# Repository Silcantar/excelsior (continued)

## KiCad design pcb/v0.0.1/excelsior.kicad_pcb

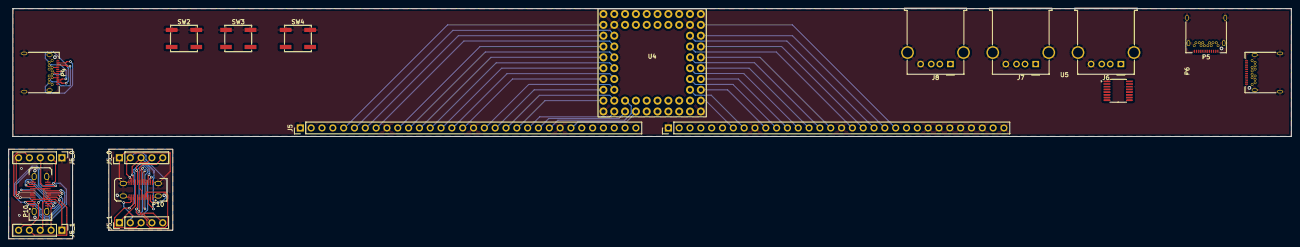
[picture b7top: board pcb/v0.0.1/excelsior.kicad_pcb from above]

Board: 2 copper layers, 301.0 x 54.0 mm, 19 parts (0 on the bottom side), 74 nets.

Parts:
J5: Conn_01x40_Socket; PinHeader_1x32_P2.54mm_Vertical
J5_0, J5_0#2, J5_1, J5_1#2: Conn_01x12; PinHeader_1x05_P2.54mm_Vertical
J6: USB_Hub4_FDD; USB_A_Molex_67643_Horizontal
J7: USB_Hub3; USB_A_Molex_67643_Horizontal
J8: USB_Hub2; USB_A_Molex_67643_Horizontal
J9: Conn_01x16_Socket; PinHeader_1x32_P2.54mm_Vertical
P4: Left_Peripheral; USB_C_Receptacle_Amphenol_12401548E4-2A
P5: Host_Port; USB_C_Receptacle_Amphenol_12401548E4-2A
P6: Right_Peripheral; USB_C_Receptacle_Amphenol_12401548E4-2A
P10, P10#2: USB_C_Receptacle; USB_C_Receptacle_JAE_DX07S024WJ3R400
SW2, SW3, SW4: SW_Push; SW_SPST_EVPBF
U4: PGA2350; pga2350
U5: CH334R; QSOP-16_3.9x4.9mm_P0.635mm

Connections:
/Excelsior_PGA2350/3V3: J9.31, U4.3V3
/Excelsior_PGA2350/BOOT: SW4.2, U4.BS (BOOTSEL)
/Excelsior_PGA2350/CH_RST: SW2.2, U5.9 (~RESET/CDP)
/Excelsior_PGA2350/CS: J5.8, P4.A3 (TX1-), P4.B3 (TX2-), P6.A3 (TX1-), P6.B3 (TX2-), U4.05 (GP05)
/Excelsior_PGA2350/DM1+: U4.U+ (USB_D+), U5.8 (DP1+)
/Excelsior_PGA2350/DM1-: U4.U- (USB_D-), U5.7 (DM1-)
/Excelsior_PGA2350/DM2+: J8.3 (D+), U5.6 (DP2+)
/Excelsior_PGA2350/DM2-: J8.2 (D-), U5.5 (DM2-)
/Excelsior_PGA2350/DM3+: J7.3 (D+), U5.4 (DP3+)
/Excelsior_PGA2350/DM3-: J7.2 (D-), U5.3 (DM3-)
/Excelsior_PGA2350/DM4+: J6.3 (D+), U5.2 (DP4+)
/Excelsior_PGA2350/DM4-: J6.2 (D-), U5.1 (DM4-)
/Excelsior_PGA2350/GND: J5.1, J5.9, J5.17, J5.25, J6.4 (GND), J6.5 (Shield), J7.4 (GND), J7.5 (Shield), J8.4 (GND), J8.5 (Shield), J9.1, J9.9, J9.17, J9.25, J9.26, J9.27, J9.28, J9.29, J9.30, J9.32, P4.A1 (GND), P4.A12 (GND), P4.B1 (GND), P4.B12 (GND), P4.S1 (SHIELD), P5.A1 (GND), P5.A12 (GND), P5.B1 (GND), P5.B12 (GND), P5.S1 (SHIELD), P6.A1 (GND), P6.A12 (GND), P6.B1 (GND), P6.B12 (GND), P6.S1 (SHIELD), SW2.1, SW3.1, SW4.1, U4.G (GND), U5.14 (GND)
/Excelsior_PGA2350/GP06: J5.10, U4.06 (GP06)
/Excelsior_PGA2350/GP07: J5.11, U4.07 (GP07)
/Excelsior_PGA2350/GP08: J5.12, U4.08 (GP08)
/Excelsior_PGA2350/GP09: J5.13, U4.09 (GP09)
/Excelsior_PGA2350/GP10: J5.14, U4.10 (GP10)
/Excelsior_PGA2350/GP11: J5.15, U4.11 (GP11)
/Excelsior_PGA2350/GP12: J5.16, U4.12 (GP12)
/Excelsior_PGA2350/GP13: J5.18, U4.13 (GP13)
/Excelsior_PGA2350/GP14: J5.19, U4.14 (GP14)
/Excelsior_PGA2350/GP15: J5.20, U4.15 (GP15)
/Excelsior_PGA2350/GP16: J5.21, U4.16 (GP16)
/Excelsior_PGA2350/GP17: J5.22, U4.17 (GP17)
/Excelsior_PGA2350/GP18: J5.23, U4.18 (GP18)
/Excelsior_PGA2350/GP19: J5.24, U4.19 (GP19)
/Excelsior_PGA2350/GP20: J5.26, U4.20 (GP20)
/Excelsior_PGA2350/GP21: J5.27, U4.21 (GP21)
/Excelsior_PGA2350/GP22: J5.28, U4.22 (GP22)
/Excelsior_PGA2350/GP23: J5.29, U4.23 (GP23)
/Excelsior_PGA2350/GP24: J5.30, U4.24 (GP24)
/Excelsior_PGA2350/GP25: J5.31, U4.25 (GP25)
/Excelsior_PGA2350/GP26: J5.32, U4.26 (GP26)
/Excelsior_PGA2350/GP27: J9.2, U4.27 (GP27)
/Excelsior_PGA2350/GP28: J9.3, U4.28 (GP28)
/Excelsior_PGA2350/GP29: J9.4, U4.29 (GP29)
/Excelsior_PGA2350/GP30: J9.5, U4.30 (GP30)
/Excelsior_PGA2350/GP31: J9.6, U4.31 (GP31)
/Excelsior_PGA2350/GP32: J9.7, U4.32 (GP32)
/Excelsior_PGA2350/GP33: J9.8, U4.33 (GP33)
/Excelsior_PGA2350/GP34: J9.10, U4.34 (GP34)
/Excelsior_PGA2350/GP35: J9.11, U4.35 (GP35)
/Excelsior_PGA2350/GP36: J9.12, U4.36 (GP36)
/Excelsior_PGA2350/GP37: J9.13, U4.37 (GP37)
/Excelsior_PGA2350/GP38: J9.14, U4.38 (GP38)
/Excelsior_PGA2350/GP39: J9.15, U4.39 (GP39)
/Excelsior_PGA2350/GP40: J9.16, U4.40 (GP40)
/Excelsior_PGA2350/GP41: J9.18, U4.41 (GP41)
/Excelsior_PGA2350/GP42: J9.19, U4.42 (GP42)
/Excelsior_PGA2350/GP43: J9.20, U4.43 (GP43)
/Excelsior_PGA2350/GP44: J9.21, U4.44 (GP44)
/Excelsior_PGA2350/GP45: J9.22, U4.45 (GP45)
/Excelsior_PGA2350/GP46: J9.23, U4.46 (GP46)
/Excelsior_PGA2350/GP47: J9.24, U4.47 (GP47)
/Excelsior_PGA2350/HOST_D+: P5.A6 (D+), P5.B6 (D+), U5.11 (DPU+)
/Excelsior_PGA2350/HOST_D-: P5.A7 (D-), P5.B7 (D-), U5.10 (DMU-)
/Excelsior_PGA2350/INTA: J5.3, P4.A10 (RX2-), P4.B10 (RX1-), P6.A10 (RX2-), P6.B10 (RX1-), U4.00 (GP00)
/Excelsior_PGA2350/INTB: J5.4, P4.A11 (RX2+), P4.B11 (RX1+), P6.A11 (RX2+), P6.B11 (RX1+), U4.01 (GP01)
/Excelsior_PGA2350/MISO: J5.7, P4.A6 (D+), P4.B6 (D+), P6.A6 (D+), P6.B6 (D+), U4.04 (GP04)
/Excelsior_PGA2350/MOSI: J5.6, P4.A7 (D-), P4.B7 (D-), P6.A7 (D-), P6.B7 (D-), U4.03 (GP03)
/Excelsior_PGA2350/RESET: SW3.2, U4.R (RUN)
/Excelsior_PGA2350/SCK: J5.5, P4.A2 (TX1+), P4.B2 (TX2+), P6.A2 (TX1+), P6.B2 (TX2+), U4.02 (GP02)
/Excelsior_PGA2350/VBUS: J5.2, J6.1 (VBUS), J7.1 (VBUS), J8.1 (VBUS), P4.A4 (VBUS), P4.A9 (VBUS), P4.B4 (VBUS), P4.B9 (VBUS), P5.A4 (VBUS), P5.A9 (VBUS), P5.B4 (VBUS), P5.B9 (VBUS), P6.A4 (VBUS), P6.A9 (VBUS), P6.B4 (VBUS), P6.B9 (VBUS), U4.3EN (3V3_EN), U4.VBB (VBUS), U5.12 (V5)
/USB Breakout/2: J5_0.2, J5_0#2.2, P10.A2 (TX1+), P10.B2 (TX2+), P10#2.A2 (TX1+), P10#2.B2 (TX2+)
/USB Breakout/3: J5_0.3, J5_0#2.3, P10.A3 (TX1-), P10.B3 (TX2-), P10#2.A3 (TX1-), P10#2.B3 (TX2-)
/USB Breakout/5: J5_0.4, J5_0#2.4, P10.A5 (CC1), P10.B5 (CC2), P10#2.A5 (CC1), P10#2.B5 (CC2)
/USB Breakout/6: J5_0.5, J5_0#2.5, P10.A6 (D+), P10.B6 (D+), P10#2.A6 (D+), P10#2.B6 (D+)
/USB Breakout/7: J5_1.5, J5_1#2.5, P10.A7 (D-), P10.B7 (D-), P10#2.A7 (D-), P10#2.B7 (D-)
/USB Breakout/8: J5_1.4, J5_1#2.4, P10.A8 (SBU1), P10.B8 (SBU2), P10#2.A8 (SBU1), P10#2.B8 (SBU2)
/USB Breakout/10: J5_1.3, J5_1#2.3, P10.A10 (RX2-), P10.B10 (RX1-), P10#2.A10 (RX2-), P10#2.B10 (RX1-)
/USB Breakout/11: J5_1.2, J5_1#2.2, P10.A11 (RX2+), P10.B11 (RX1+), P10#2.A11 (RX2+), P10#2.B11 (RX1+)
/USB Breakout/GND: J5_0.1, J5_0#2.1, P10.A1 (GND), P10.A12 (GND), P10.B1 (GND), P10.B12 (GND), P10.S1 (SHIELD), P10#2.A1 (GND), P10#2.A12 (GND), P10#2.B1 (GND), P10#2.B12 (GND), P10#2.S1 (SHIELD)
/USB Breakout/VBUS: J5_1.1, J5_1#2.1, P10.A4 (VBUS), P10.A9 (VBUS), P10.B4 (VBUS), P10.B9 (VBUS), P10#2.A4 (VBUS), P10#2.A9 (VBUS), P10#2.B4 (VBUS), P10#2.B9 (VBUS)

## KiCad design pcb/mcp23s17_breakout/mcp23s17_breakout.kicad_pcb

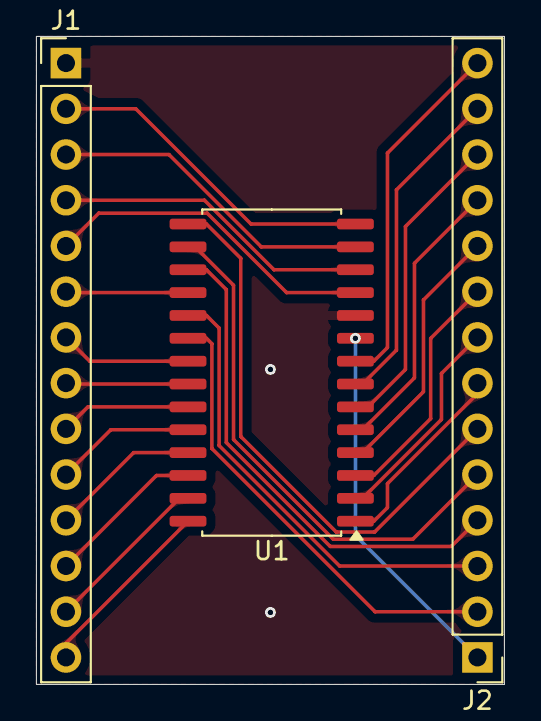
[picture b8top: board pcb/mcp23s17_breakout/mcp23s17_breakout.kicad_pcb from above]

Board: 2 copper layers, 26.0 x 36.0 mm, 3 parts (0 on the bottom side), 28 nets.

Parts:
J1, J2: Conn_01x14; PinHeader_1x14_P2.54mm_Vertical
U1: MCP23017_SO; SOIC-28W_7.5x17.9mm_P1.27mm

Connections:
/A0: J2.19 (Pin_6), U1.15 (A0)
/A1: J2.18 (Pin_5), U1.16 (A1)
/A2: J2.17 (Pin_4), U1.17 (A2)
/CS: J1.04 (Pin_5), U1.11 (~CS)
/GND: J1.G (Pin_1), U1.10 (VSS)
/GPA0: J1.06 (Pin_7), U1.21 (GPA0)
/GPA1: J1.07 (Pin_8), U1.22 (GPA1)
/GPA2: J1.08 (Pin_9), U1.23 (GPA2)
/GPA3: J1.09 (Pin_10), U1.24 (GPA3)
/GPA4: J1.10 (Pin_11), U1.25 (GPA4)
/GPA5: J1.11 (Pin_12), U1.26 (GPA5)
/GPA6: J1.12 (Pin_13), U1.27 (GPA6)
/GPA7: J1.13 (Pin_14), U1.28 (GPA7)
/GPB0: J2.20 (Pin_7), U1.1 (GPB0)
/GPB1: J2.21 (Pin_8), U1.2 (GPB1)
/GPB2: J2.22 (Pin_9), U1.3 (GPB2)
/GPB3: J2.23 (Pin_10), U1.4 (GPB3)
/GPB4: J2.24 (Pin_11), U1.5 (GPB4)
/GPB5: J2.25 (Pin_12), U1.6 (GPB5)
/GPB6: J2.26 (Pin_13), U1.7 (GPB6)
/GPB7: J2.27 (Pin_14), U1.8 (GPB7)
/INTA: J2.15 (Pin_2), U1.20 (INTA)
/INTB: J2.16 (Pin_3), U1.19 (INTB)
/RST: J1.05 (Pin_6), U1.18 (~RESET)
/SCK: J1.03 (Pin_4), U1.12 (SCK)
/SI: J1.02 (Pin_3), U1.13 (SI)
/SO: J1.01 (Pin_2), U1.14 (SO)
/VBUS: J2.14 (Pin_1), U1.9 (VDD)

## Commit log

2025-05-09 Add KLE screenshot.
2025-05-09 Update readme and KLE screenshot.
2025-05-09 Update readme, add KLE json.
2025-05-09 Update readme.
2025-05-09 Add preliminary PCB design.
2025-05-12 Continue work on PCB design.
2025-05-13 Continue work on PCBs, add Gerber files.
2025-05-13 Continue work on PCBs, add gitignore and remove backup files.
2025-05-14 Continue work on PCBs.
2025-05-14 Fresh start on PCBs.
2025-05-15 Add breakout boards for MCP23S17 and HDMI connector.
2025-05-15 Restructure PCB folder.
2025-05-20 - Update main Readme. - Add folders for case CAD and KMK files. - In the PCBs, fix VBUS and GND being removed from connectors. - Add PCB readme.
2025-05-20 KMK firmware: add keymap and IO pinout.
2025-05-21 - Change pogo pin connectors on opposite sides from rotated to mirrored. - Add lots of firmware code. - Add VSCode settings to gitignore.
2025-05-23 Add FreeCAD project for case.
2025-05-23 Update gitignore.
2025-05-23 Add wildcards to gitignore.
2025-05-26 Finish main plate except stabilizer cutouts.
2025-05-29 Add stabilizer cutouts to main plate model.
2025-05-31 Add YUZU json export and update readme.
2025-06-02 Add knob image for KLE.
2025-06-02 Crop knob image.
2025-06-02 Update KLE screenshot.
2025-06-03 Start transposing keymaps.
2025-06-03 Continue transposing keymaps.
2025-06-04 Finish keymaps; add necessary Adafruit libraries.
2025-06-16 Add boot.py for setting CircuitPython drive name.
2025-06-16 Remove KMK files that have been moved to kmk_excelsior repository.
